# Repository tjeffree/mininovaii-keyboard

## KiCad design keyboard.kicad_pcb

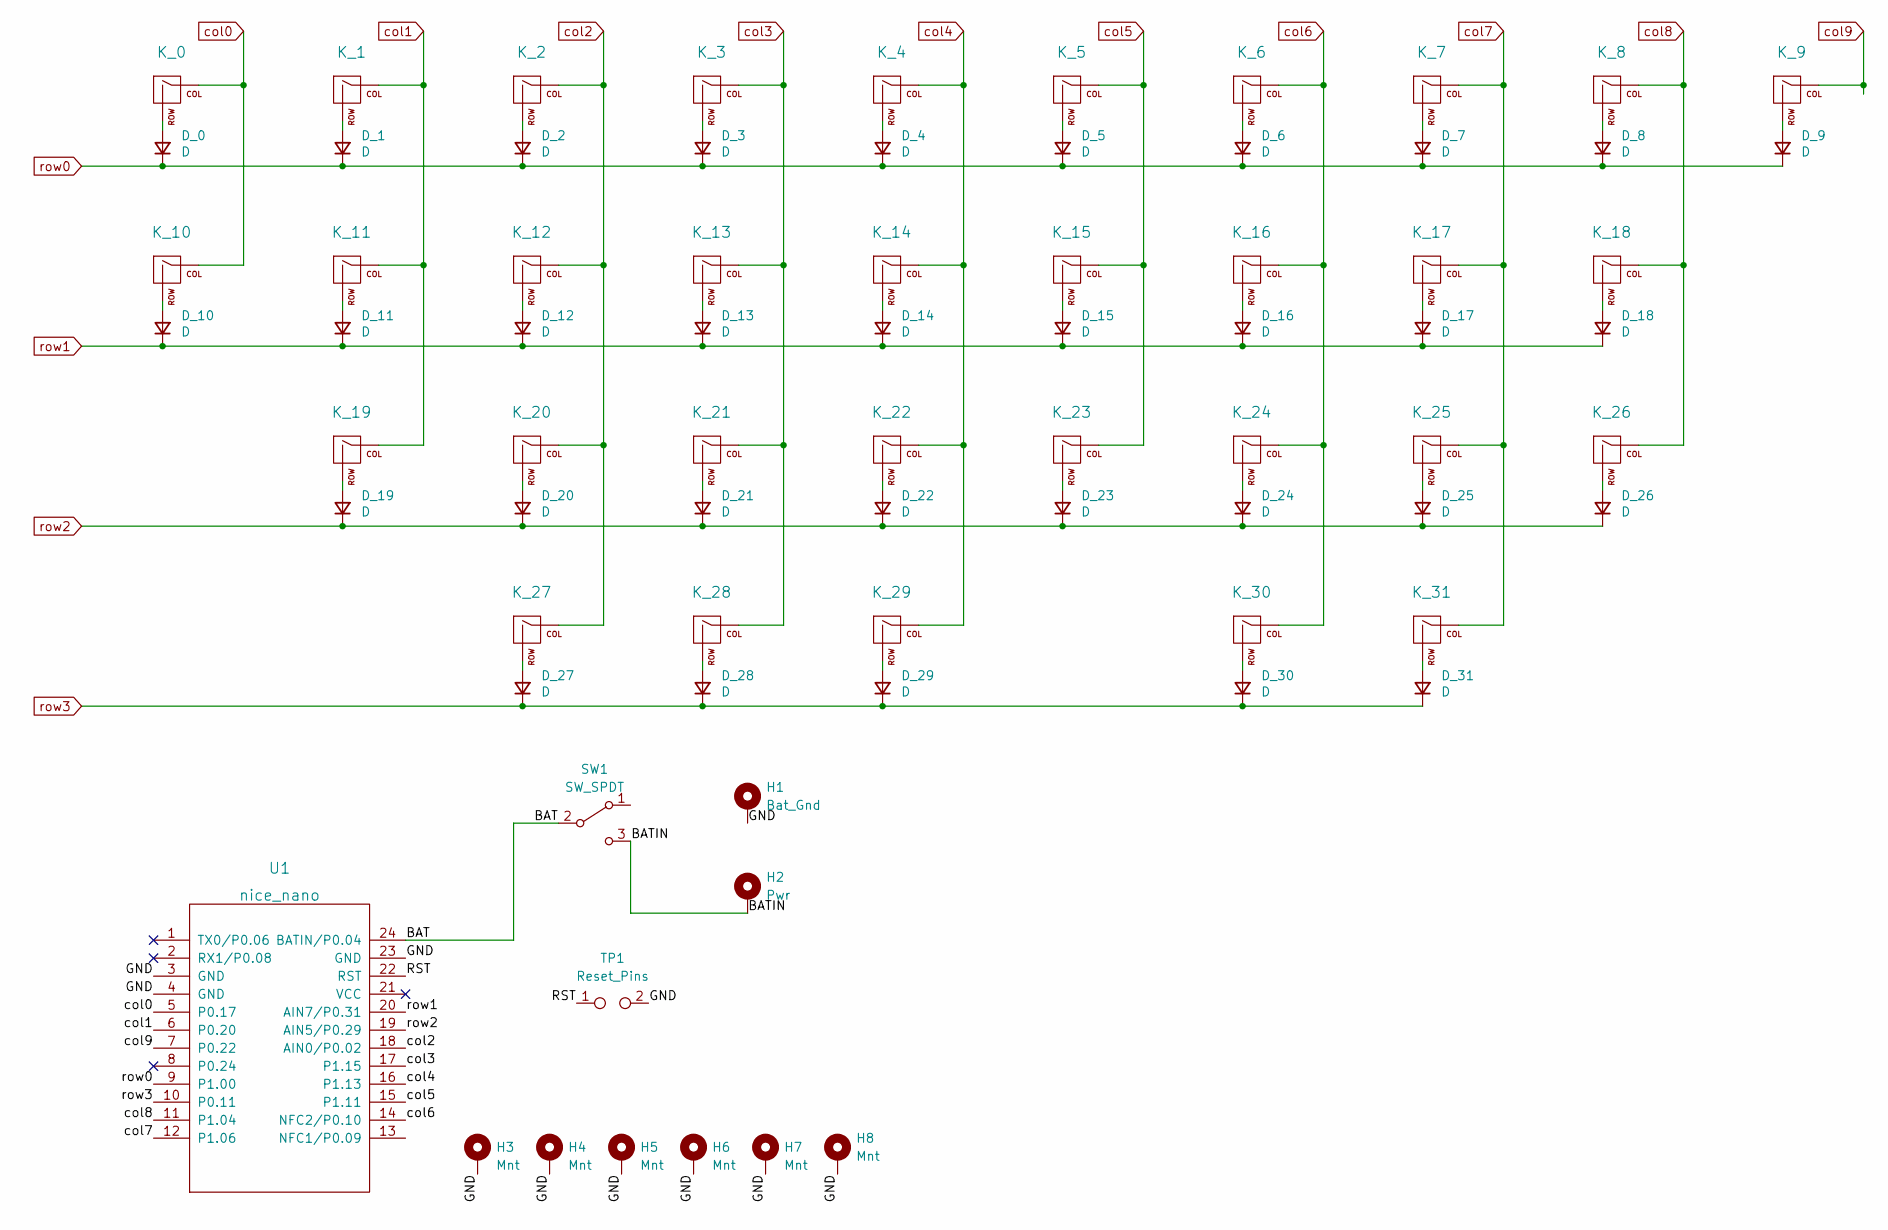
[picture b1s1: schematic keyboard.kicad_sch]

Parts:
D_0, D_1, D_2, D_3, D_4, D_5, D_6, D_7, D_8, D_9, D_10, D_11, D_12, D_13, D_14, D_15, D_16, D_17, D_18, D_19, D_20, D_21, D_22, D_23, D_24, D_25, D_26, D_27, D_28, D_29, D_30, D_31: D; Diode-dual
H1: Bat_Gnd; TestPoint_THTPad_D2.0mm_Drill1.0mm
H2: Pwr; TestPoint_THTPad_D2.0mm_Drill1.0mm
H3, H4, H5, H6, H7, H8: Mnt; TestPoint_THTPad_D4.0mm_Drill2.0mm
K_0, K_1, K_2, K_3, K_4, K_5, K_6, K_7, K_8, K_9, K_10, K_11, K_12, K_13, K_14, K_15, K_16, K_17, K_18, K_19, K_20, K_21, K_22, K_23, K_24, K_25, K_26, K_27, K_28, K_30, K_31: KEYSW; SW_MX_PG1350_NoLed
K_29: KEYSW; MX-Alps-Choc-2U
SW1: SW_SPDT; SW_Slide_1P2T_CK_OS102011MS2Q
TP1: Reset_Pins; ResetSW
U1: nice_nano

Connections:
/BAT: SW1.2 (B), U1.24 (BATIN/P0.04)
/BATIN: H2.1, SW1.3 (C); also elsewhere on the board
/GND: H1.1, H3.1, H4.1, H5.1, H6.1, H7.1, H8.1, TP1.2, U1.3 (GND), U1.4 (GND), U1.23 (GND); also elsewhere on the board
/RST: TP1.1, U1.22 (RST)
unnamed: D_0.2 (A), K_0.2 (ROW)
unnamed: D_1.2 (A), K_1.2 (ROW)
unnamed: D_2.2 (A), K_2.2 (ROW)
unnamed: D_3.2 (A), K_3.2 (ROW)
unnamed: D_4.2 (A), K_4.2 (ROW)
unnamed: D_5.2 (A), K_5.2 (ROW)
unnamed: D_6.2 (A), K_6.2 (ROW)
unnamed: D_7.2 (A), K_7.2 (ROW)
unnamed: D_8.2 (A), K_8.2 (ROW)
unnamed: D_9.2 (A), K_9.2 (ROW)
unnamed: D_10.2 (A), K_10.2 (ROW)
unnamed: D_11.2 (A), K_11.2 (ROW)
unnamed: D_12.2 (A), K_12.2 (ROW)
unnamed: D_13.2 (A), K_13.2 (ROW)
unnamed: D_14.2 (A), K_14.2 (ROW)
unnamed: D_15.2 (A), K_15.2 (ROW)
unnamed: D_16.2 (A), K_16.2 (ROW)
unnamed: D_17.2 (A), K_17.2 (ROW)
unnamed: D_18.2 (A), K_18.2 (ROW)
unnamed: D_19.2 (A), K_19.2 (ROW)
unnamed: D_20.2 (A), K_20.2 (ROW)
unnamed: D_21.2 (A), K_21.2 (ROW)
unnamed: D_22.2 (A), K_22.2 (ROW)
unnamed: D_23.2 (A), K_23.2 (ROW)
unnamed: D_24.2 (A), K_24.2 (ROW)
unnamed: D_25.2 (A), K_25.2 (ROW)
unnamed: D_26.2 (A), K_26.2 (ROW)
unnamed: D_27.2 (A), K_27.2 (ROW)
unnamed: D_28.2 (A), K_28.2 (ROW)
unnamed: D_29.2 (A), K_29.2 (ROW)
unnamed: D_30.2 (A), K_30.2 (ROW)
unnamed: D_31.2 (A), K_31.2 (ROW)
col0: K_0.1 (COL), K_10.1 (COL), U1.5 (P0.17)
col1: K_1.1 (COL), K_11.1 (COL), K_19.1 (COL), U1.6 (P0.20)
col2: K_2.1 (COL), K_12.1 (COL), K_20.1 (COL), K_27.1 (COL), U1.18 (AIN0/P0.02)
col3: K_3.1 (COL), K_13.1 (COL), K_21.1 (COL), K_28.1 (COL), U1.17 (P1.15)
col4: K_4.1 (COL), K_14.1 (COL), K_22.1 (COL), K_29.1 (COL), U1.16 (P1.13)
col5: K_5.1 (COL), K_15.1 (COL), K_23.1 (COL), U1.15 (P1.11)
col6: K_6.1 (COL), K_16.1 (COL), K_24.1 (COL), K_30.1 (COL), U1.14 (NFC2/P0.10)
col7: K_7.1 (COL), K_17.1 (COL), K_25.1 (COL), K_31.1 (COL), U1.12 (P1.06)
col8: K_8.1 (COL), K_18.1 (COL), K_26.1 (COL), U1.11 (P1.04)
col9: K_9.1 (COL), U1.7 (P0.22)
row0: D_0.1 (K), D_1.1 (K), D_2.1 (K), D_3.1 (K), D_4.1 (K), D_5.1 (K), D_6.1 (K), D_7.1 (K), D_8.1 (K), D_9.1 (K), U1.9 (P1.00)
row1: D_10.1 (K), D_11.1 (K), D_12.1 (K), D_13.1 (K), D_14.1 (K), D_15.1 (K), D_16.1 (K), D_17.1 (K), D_18.1 (K), U1.20 (AIN7/P0.31)
row2: D_19.1 (K), D_20.1 (K), D_21.1 (K), D_22.1 (K), D_23.1 (K), D_24.1 (K), D_25.1 (K), D_26.1 (K), U1.19 (AIN5/P0.29)
row3: D_27.1 (K), D_28.1 (K), D_29.1 (K), D_30.1 (K), D_31.1 (K), U1.10 (P0.11)

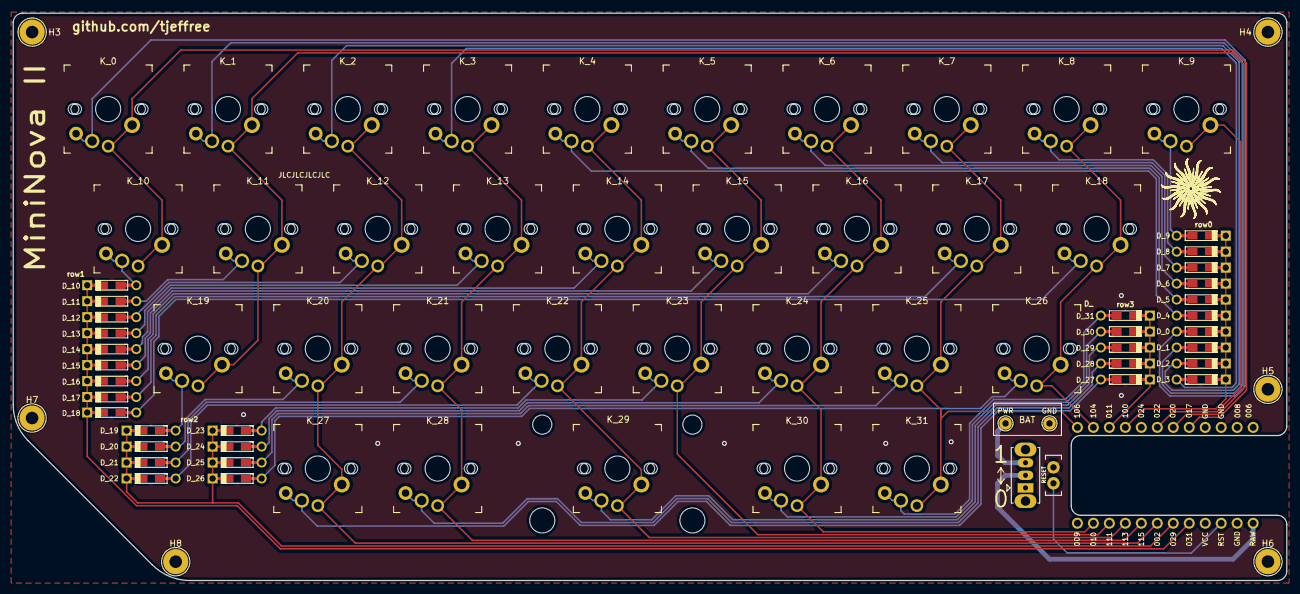
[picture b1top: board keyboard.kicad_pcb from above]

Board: 2 copper layers, 202.5 x 90.2 mm, 75 parts (0 on the bottom side), 50 nets.

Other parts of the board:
GND: Bat_Gnd; TestPoint_THTPad_D2.0mm_Drill1.0mm
PWR: Pwr; TestPoint_THTPad_D2.0mm_Drill1.0mm

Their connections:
/BATIN: PWR.1; also elsewhere on the board
/GND: GND.1; also elsewhere on the board

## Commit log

2022-03-07 Cut corner version
2022-03-11 First gerber
2022-03-14 Add reset pins
2022-03-14 Add prod gerber
2022-04-07 Update PCB labels Add DXF
